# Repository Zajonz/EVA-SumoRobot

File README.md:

### EVA-SumoRobot

## ⚡ Overview
```
This robot is based on:

- 🧠 ESP32-S3 WROOM – main controller

- ⚙️ Pololu 37D motors – powerful drive system

- 🔌 2× Cytron MD13S – motor drivers

- 👀 2× E18-D80NK IR sensors – front detection

- 🔋 Designed for efficiency, stability and quick reaction times

# Current achievements:

- 🏆 Reached group stage twice in competitions

- (More soon as upgrades roll out)
```

## 🛠️ Current Features
```
- Fast dual-motor drive system

- Basic attack/escape behaviour logic

- Real-time sensor-based decision making

- Clean modular firmware on ESP32-S3

- Simple sensor calibration

- Future-proof structure for upgrades
```

## 🚀 Planned Upgrades (Next Versions)
```
- I’m actively upgrading the entire platform:
```

# 🔧 Electronics
```
- Full SMD PCB redesign

- Adding VL53L1X ToF sensors for precise distance measurement

- Using ATtiny402 to convert ToF readings into clean digital signals

- Custom H-bridge motor drivers for higher efficiency

- Better power distribution & noise handling
```

# 🧠 Software
```
- ⚙️ PID-based motion control

- Advanced strategy layers (angle attack, zone control, adaptive behavior)

- Real-time monitoring & debugging support
```

## 🧩 Components Used
```
- ESP32-S3 WROOM

- Pololu 37D 12V motors

- Cytron MD13S motor drivers

- E18-D80NK IR sensors

- Custom 3D-printed & machined parts
```

## 📚 Tech Stack
```
- Firmware: C++ / Arduino framework on PlatformIO

- Electronics: KiCad (upcoming SMD board)

- Mechanical design: Autodesk Fusion 360
```

## 🧪 Future Experiments
```
- Faster motor ramping

- Anti-spin logic

- Multi-sensor fusion

- Opponent tracking with ToF array

- Low-latency mode for ESP32-S3
```

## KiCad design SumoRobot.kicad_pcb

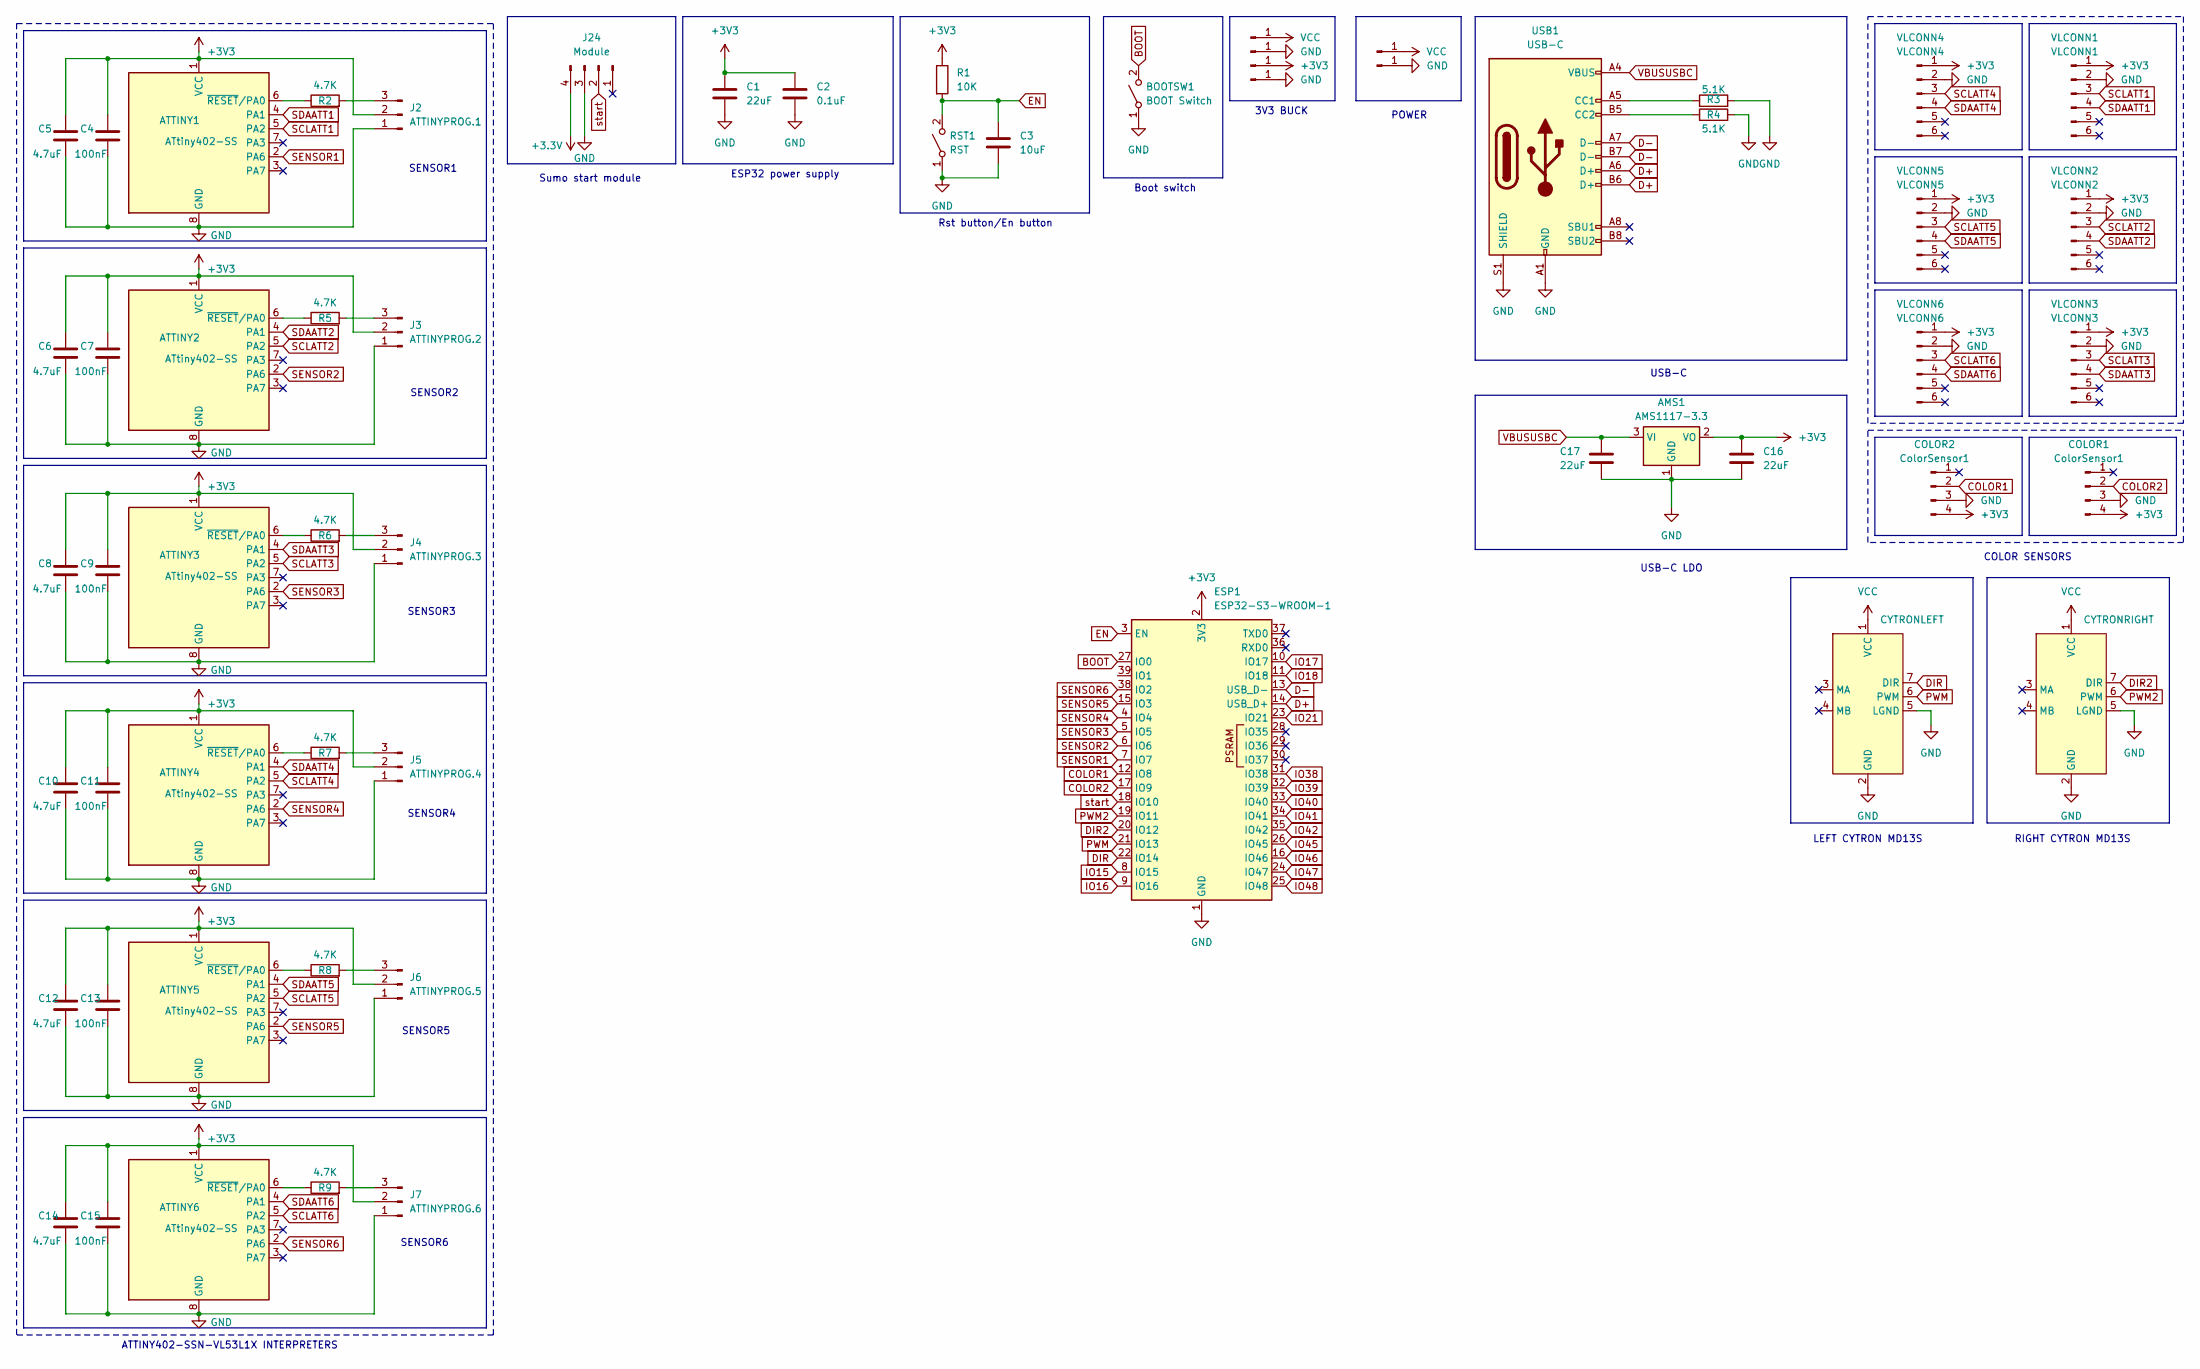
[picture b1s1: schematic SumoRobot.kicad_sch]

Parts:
3V3: 3V3; PinHeader_1x01_P2.54mm_Vertical
AMS1: AMS1117-3.3; SOT-223-3_TabPin2
ATTINY1, ATTINY2, ATTINY3, ATTINY4, ATTINY5, ATTINY6: ATtiny402-SS; SOIC-8_3.9x4.9mm_P1.27mm
BOOTSW1: BOOT Switch; SW_SPST_FSMSM
C1, C16, C17: 22uF; C_0805_2012Metric
C2: 0.1uF; C_0805_2012Metric
C3: 10uF; C_0805_2012Metric
C4, C7, C9, C11, C13, C15: 100nF; C_0805_2012Metric
C5, C6, C8, C10, C12, C14: 4.7uF; C_0805_2012Metric
COLOR1, COLOR2: ColorSensor1; JST_EH_B4B-EH-A_1x04_P2.50mm_Vertical
ESP1: ESP32-S3-WROOM-1; ESP32-S3-WROOM-1U
GND1: 3V3; SolderWirePad_1x01_SMD_5x10mm
J2: ATTINYPROG.1; JST_EH_B3B-EH-A_1x03_P2.50mm_Vertical
J3: ATTINYPROG.2; JST_EH_B3B-EH-A_1x03_P2.50mm_Vertical
J4: ATTINYPROG.3; JST_EH_B3B-EH-A_1x03_P2.50mm_Vertical
J5: ATTINYPROG.4; JST_EH_B3B-EH-A_1x03_P2.50mm_Vertical
J6: ATTINYPROG.5; JST_EH_B3B-EH-A_1x03_P2.50mm_Vertical
J7: ATTINYPROG.6; JST_EH_B3B-EH-A_1x03_P2.50mm_Vertical
J15, J17: 3V3; PinHeader_1x01_P2.54mm_Vertical
J24: Module; PinHeader_1x04_P2.54mm_Vertical
Left-Cytron1: CYTRONRIGHT; MD13S-Poprawione
R1: 10K; R_0805_2012Metric
R2, R5, R6, R7, R8, R9: 4.7K; R_0805_2012Metric
R3, R4: 5.1K; R_0805_2012Metric
RST1: RST; SW_SPST_FSMSM
Right-Cytron1: CYTRONLEFT; MD13S-Poprawione
USB1: USB-C; USB_C_Receptacle_GCT_USB4105-xx-A_16P_TopMnt_Horizontal
VCC1: 3V3; PinHeader_1x01_P2.54mm_Vertical
VCC2: 3V3; SolderWirePad_1x01_SMD_5x10mm
VLCONN1: VLCONN1; JST_EH_B6B-EH-A_1x06_P2.50mm_Vertical
VLCONN2: VLCONN2; JST_EH_B6B-EH-A_1x06_P2.50mm_Vertical
VLCONN3: VLCONN3; JST_EH_B6B-EH-A_1x06_P2.50mm_Vertical
VLCONN4: VLCONN4; JST_EH_B6B-EH-A_1x06_P2.50mm_Vertical
VLCONN5: VLCONN5; JST_EH_B6B-EH-A_1x06_P2.50mm_Vertical
VLCONN6: VLCONN6; JST_EH_B6B-EH-A_1x06_P2.50mm_Vertical

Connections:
+3.3V: J24.4
+3V3: 3V3.1, AMS1.2 (VO), ATTINY1.1 (VCC), ATTINY2.1 (VCC), ATTINY3.1 (VCC), ATTINY4.1 (VCC), ATTINY5.1 (VCC), ATTINY6.1 (VCC), C1.1, C2.1, C4.1, C5.1, C6.1, C7.1, C8.1, C9.1, C10.1, C11.1, C12.1, C13.1, C14.1, C15.1, C16.1, COLOR1.4, COLOR2.4, ESP1.2 (3V3), J2.2, J3.2, J4.2, J5.2, J6.2, J7.2, R1.1, VLCONN1.1, VLCONN2.1, VLCONN3.1, VLCONN4.1, VLCONN5.1, VLCONN6.1
BOOT: BOOTSW1.2 (B), ESP1.27 (IO0)
COLOR1: COLOR2.2, ESP1.12 (IO8)
COLOR2: COLOR1.2, ESP1.17 (IO9)
D+: ESP1.14 (USB_D+), USB1.A6 (D+), USB1.B6 (D+)
D-: ESP1.13 (USB_D-), USB1.A7 (D-), USB1.B7 (D-)
DIR: ESP1.22 (IO14), Right-Cytron1.7 (DIR)
DIR2: ESP1.20 (IO12), Left-Cytron1.7 (DIR)
EN: C3.1, ESP1.3 (EN), R1.2, RST1.2 (B)
GND: AMS1.1 (GND), ATTINY1.8 (GND), ATTINY2.8 (GND), ATTINY3.8 (GND), ATTINY4.8 (GND), ATTINY5.8 (GND), ATTINY6.8 (GND), BOOTSW1.1 (A), C1.2, C2.2, C3.2, C4.2, C5.2, C6.2, C7.2, C8.2, C9.2, C10.2, C11.2, C12.2, C13.2, C14.2, C15.2, C16.2, C17.2, COLOR1.3, COLOR2.3, ESP1.1 (GND), ESP1.40 (GND), ESP1.41 (GND), GND1.1, J2.1, J3.1, J4.1, J5.1, J6.1, J7.1, J15.1, J17.1, J24.3, Left-Cytron1.2 (GND), Left-Cytron1.5 (LGND), R3.2, R4.2, RST1.1 (A), Right-Cytron1.2 (GND), Right-Cytron1.5 (LGND), USB1.A1 (GND), USB1.A12 (GND), USB1.B1 (GND), USB1.B12 (GND), USB1.S1 (SHIELD), VLCONN1.2, VLCONN2.2, VLCONN3.2, VLCONN4.2, VLCONN5.2, VLCONN6.2
IO15: ESP1.8 (IO15)
IO16: ESP1.9 (IO16)
IO17: ESP1.10 (IO17)
IO18: ESP1.11 (IO18)
IO21: ESP1.23 (IO21)
IO38: ESP1.31 (IO38)
IO39: ESP1.32 (IO39)
IO40: ESP1.33 (IO40)
IO41: ESP1.34 (IO41)
IO42: ESP1.35 (IO42)
IO45: ESP1.26 (IO45)
IO46: ESP1.16 (IO46)
IO47: ESP1.24 (IO47)
IO48: ESP1.25 (IO48)
unnamed: ATTINY1.6 (~RESET/PA0), R2.1
unnamed: ATTINY2.6 (~RESET/PA0), R5.1
unnamed: ATTINY3.6 (~RESET/PA0), R6.1
unnamed: ATTINY4.6 (~RESET/PA0), R7.1
unnamed: ATTINY5.6 (~RESET/PA0), R8.1
unnamed: ATTINY6.6 (~RESET/PA0), R9.1
unnamed: J2.3, R2.2
unnamed: J3.3, R5.2
unnamed: J4.3, R6.2
unnamed: J5.3, R7.2
unnamed: J6.3, R8.2
unnamed: J7.3, R9.2
unnamed: R3.1, USB1.A5 (CC1)
unnamed: R4.1, USB1.B5 (CC2)
PWM: ESP1.21 (IO13), Right-Cytron1.6 (PWM)
PWM2: ESP1.19 (IO11), Left-Cytron1.6 (PWM)
SCLATT1: ATTINY1.5 (PA2), VLCONN1.3
SCLATT2: ATTINY2.5 (PA2), VLCONN2.3
SCLATT3: ATTINY3.5 (PA2), VLCONN3.3
SCLATT4: ATTINY4.5 (PA2), VLCONN4.3
SCLATT5: ATTINY5.5 (PA2), VLCONN5.3
SCLATT6: ATTINY6.5 (PA2), VLCONN6.3
SDAATT1: ATTINY1.4 (PA1), VLCONN1.4
SDAATT2: ATTINY2.4 (PA1), VLCONN2.4
SDAATT3: ATTINY3.4 (PA1), VLCONN3.4
SDAATT4: ATTINY4.4 (PA1), VLCONN4.4
SDAATT5: ATTINY5.4 (PA1), VLCONN5.4
SDAATT6: ATTINY6.4 (PA1), VLCONN6.4
SENSOR1: ATTINY1.2 (PA6), ESP1.7 (IO7)
SENSOR2: ATTINY2.2 (PA6), ESP1.6 (IO6)
SENSOR3: ATTINY3.2 (PA6), ESP1.5 (IO5)
SENSOR4: ATTINY4.2 (PA6), ESP1.4 (IO4)
SENSOR5: ATTINY5.2 (PA6), ESP1.15 (IO3)
SENSOR6: ATTINY6.2 (PA6), ESP1.38 (IO2)
VBUSUSBC: AMS1.3 (VI), C17.1, USB1.A4 (VBUS), USB1.A9 (VBUS), USB1.B4 (VBUS), USB1.B9 (VBUS)
VCC: Left-Cytron1.1 (VCC), Right-Cytron1.1 (VCC), VCC1.1, VCC2.1
start: ESP1.18 (IO10), J24.2

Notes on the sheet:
ESP32 power supply
POWER
3V3 BUCK
Rst button/En button
USB-C LDO
Sumo start module
SENSOR5
USB-C
SENSOR4
RIGHT CYTRON MD13S
Boot switch
LEFT CYTRON MD13S
SENSOR1
COLOR SENSORS
ATTINY402-SSN-VL53L1X INTERPRETERS
SENSOR2
SENSOR6
SENSOR3

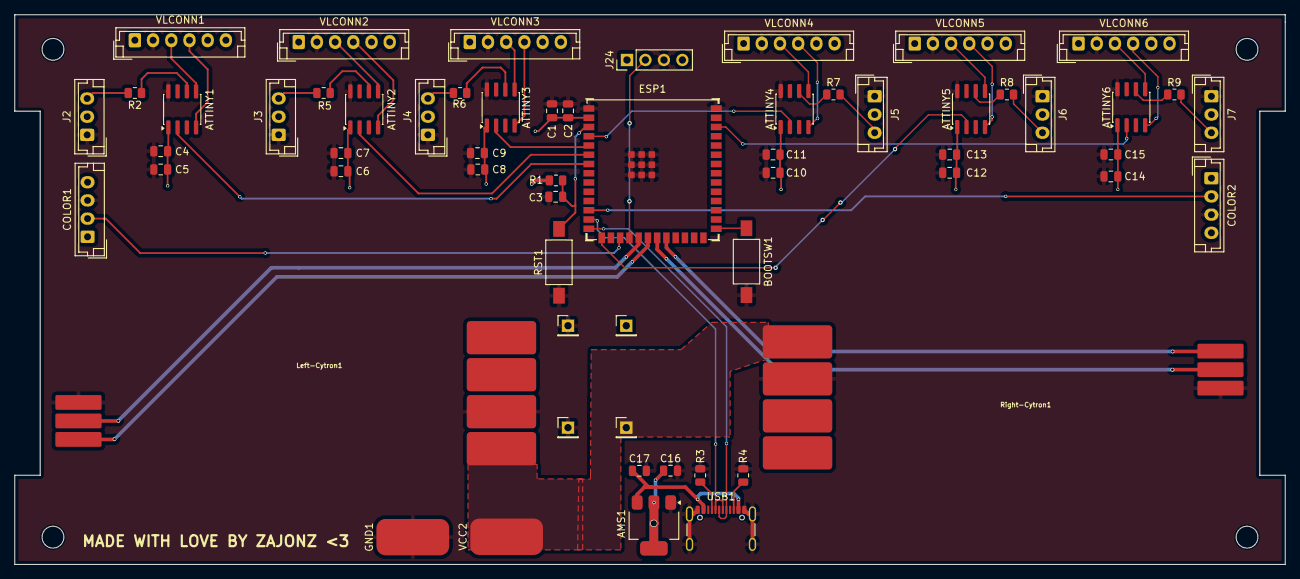
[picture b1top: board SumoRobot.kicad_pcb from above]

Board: 2 copper layers, 174.5 x 75.5 mm, 60 parts (0 on the bottom side), 47 nets.
